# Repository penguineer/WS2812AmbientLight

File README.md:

# WS2812 Ambient Light

Create an ambient light using WS2812 and a Sonoff TH10 to switch on/off the power supply.

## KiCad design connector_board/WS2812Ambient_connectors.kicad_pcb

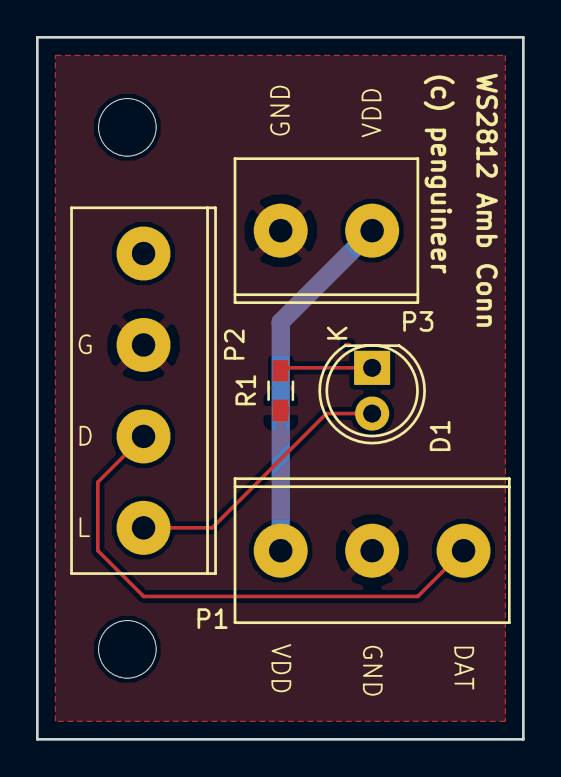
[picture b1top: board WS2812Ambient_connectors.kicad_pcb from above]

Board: 2 copper layers, 27.0 x 39.0 mm, 5 parts (0 on the bottom side), 5 nets.

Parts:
D1: LED; LED-5MM
P1: CONN_01X03; AKL_101-03
P2: CONN_01X04; AKL_101-04
P3: CONN_01X02; AKL_101-02
R1: R; R_0603_HandSoldering

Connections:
GND: P1.2, P2.2, P3.2, R1.2
unnamed: D1.1, R1.1
unnamed: D1.2, P2.4
unnamed: P1.3, P2.3
VDD: P1.1, P3.1

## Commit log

2017-12-12 Schematic and PCB for connector board
2017-12-12 DirtyPCB order
